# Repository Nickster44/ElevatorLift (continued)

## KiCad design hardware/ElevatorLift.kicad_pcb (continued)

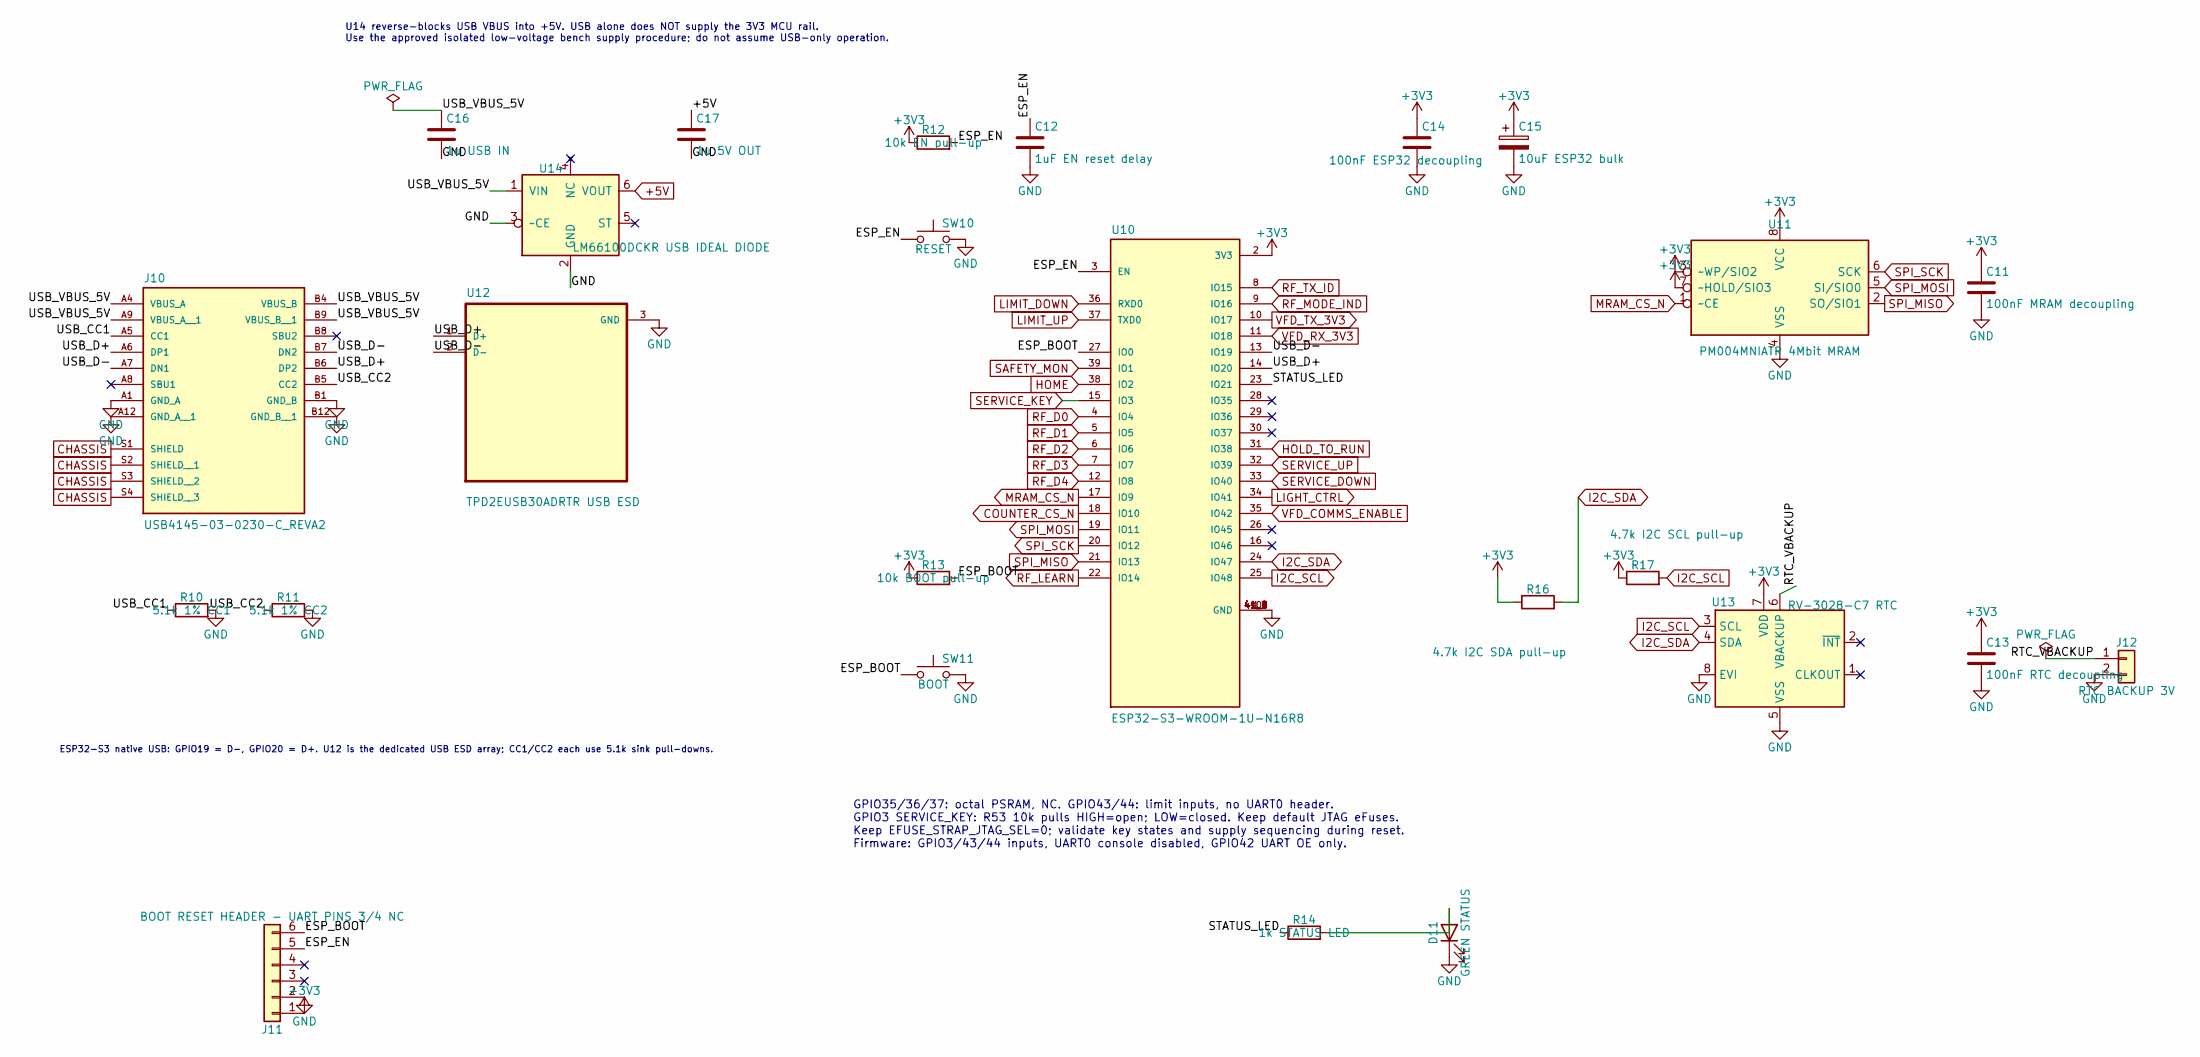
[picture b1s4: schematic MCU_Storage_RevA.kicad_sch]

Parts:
C11: 100nF MRAM decoupling; C_0603_1608Metric
C12: 1uF EN reset delay; C_0603_1608Metric
C13: 100nF RTC decoupling; C_0603_1608Metric
C14: 100nF ESP32 decoupling; C_0603_1608Metric
C15: 10uF ESP32 bulk; C_0805_2012Metric
C16: 1u USB IN; C_0603_1608Metric
C17: 1u 5V OUT; C_0603_1608Metric
D11: GREEN STATUS; LED_0603_1608Metric
J10: USB4145-03-0230-C_REVA2; GCT_USB4145-03-0230-C_REVA2
J11: BOOT RESET HEADER - UART PINS 3/4 NC; PinHeader_1x06_P2.54mm_Vertical
J12: RTC BACKUP 3V; PinHeader_1x02_P2.54mm_Vertical
R10: 5.1k 1% CC1; R_0603_1608Metric
R11: 5.1k 1% CC2; R_0603_1608Metric
R12: 10k EN pull-up; R_0603_1608Metric
R13: 10k BOOT pull-up; R_0603_1608Metric
R14: 1k STATUS LED; R_0603_1608Metric
R16: 4.7k I2C SDA pull-up; R_0603_1608Metric
R17: 4.7k I2C SCL pull-up; R_0603_1608Metric
SW10: RESET; SW_SPST_PTS810
SW11: BOOT; SW_SPST_PTS810
U10: ESP32-S3-WROOM-1U-N16R8; ESP32-S3-WROOM-1U-N16R8_CorrectedV2; MPN ESP32-S3-WROOM-1U-N16R8
U11: PM004MNIATR 4Mbit MRAM; SOIC-8_3.9x4.9mm_P1.27mm; MPN PM004MNIATR
U12: TPD2EUSB30ADRTR USB ESD; SOTFL35P100X50-3N; MPN TPD2EUSB30ADRTR
U13: RV-3028-C7 RTC; MicroCrystal_C7_SON-8_1.5x3.2mm_P0.9mm; MPN RV-3028-C7
U14: LM66100DCKR USB IDEAL DIODE; SOT-363_SC-70-6; MPN LM66100DCKR

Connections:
+3V3: C11.1, C13.1, C14.1, C15.1, J11.1, R12.1, R13.1, R16.1, R17.1, U10.2 (3V3), U11.3 (~WP/SIO2), U11.7 (~HOLD/SIO3), U11.8 (VCC), U13.7 (VDD); also elsewhere on the board
+5V: C17.1, U14.6 (VOUT); also elsewhere on the board
/MCU_Storage/ESP_BOOT: J11.6, R13.2, SW11.1, U10.27 (IO0)
/MCU_Storage/ESP_EN: C12.1, J11.5, R12.2, SW10.1, U10.3 (EN)
/MCU_Storage/RTC_VBACKUP: J12.1, U13.6 (VBACKUP)
/MCU_Storage/STATUS_LED: R14.1, U10.23 (IO21)
/MCU_Storage/USB_CC1: J10.A5 (CC1), R10.1
/MCU_Storage/USB_CC2: J10.B5 (CC2), R11.1
/MCU_Storage/USB_D+: J10.A6 (DP1), J10.B6 (DP2), U10.14 (IO20), U12.1 (D+)
/MCU_Storage/USB_D-: J10.A7 (DN1), J10.B7 (DN2), U10.13 (IO19), U12.2 (D-)
/MCU_Storage/USB_VBUS_5V: C16.1, J10.A4 (VBUS_A), J10.A9 (VBUS_A__1), J10.B4 (VBUS_B), J10.B9 (VBUS_B__1), U14.1 (VIN)
CHASSIS: J10.S1 (SHIELD), J10.S2 (SHIELD__1), J10.S3 (SHIELD__2), J10.S4 (SHIELD__3); also elsewhere on the board
COUNTER_CS_N: U10.18 (IO10); also elsewhere on the board
GND: C11.2, C12.2, C13.2, C14.2, C15.2, C16.2, C17.2, D11.1 (K), J10.A1 (GND_A), J10.A12 (GND_A__1), J10.B1 (GND_B), J10.B12 (GND_B__1), J11.2, J12.2, R10.2, R11.2, SW10.2, SW11.2, U10.1 (GND), U10.40 (GND), U10.41_1 (GND), U10.41_2 (GND), U10.41_3 (GND), U10.41_4 (GND), U10.41_5 (GND), U10.41_6 (GND), U10.41_7 (GND), U10.41_8 (GND), U10.41_9 (GND), U11.4 (VSS), U12.3 (GND), U13.5 (VSS), U13.8 (EVI), U14.2 (GND), U14.3 (~CE); also elsewhere on the board
HOLD_TO_RUN: U10.31 (IO38); also elsewhere on the board
HOME: U10.38 (IO2); also elsewhere on the board
I2C_SCL: R17.2, U10.25 (IO48), U13.3 (SCL)
I2C_SDA: R16.2, U10.24 (IO47), U13.4 (SDA)
LIGHT_CTRL: U10.34 (IO41); also elsewhere on the board
LIMIT_DOWN: U10.36 (RXD0); also elsewhere on the board
LIMIT_UP: U10.37 (TXD0); also elsewhere on the board
MRAM_CS_N: U10.17 (IO9), U11.1 (~CE)
unnamed: D11.2 (A), R14.2
RF_D0: U10.4 (IO4); also elsewhere on the board
RF_D1: U10.5 (IO5); also elsewhere on the board
RF_D2: U10.6 (IO6); also elsewhere on the board
RF_D3: U10.7 (IO7); also elsewhere on the board
RF_D4: U10.12 (IO8); also elsewhere on the board
RF_LEARN: U10.22 (IO14); also elsewhere on the board
RF_MODE_IND: U10.9 (IO16); also elsewhere on the board
RF_TX_ID: U10.8 (IO15); also elsewhere on the board
SAFETY_MON: U10.39 (IO1); also elsewhere on the board
SERVICE_DOWN: U10.33 (IO40); also elsewhere on the board
SERVICE_KEY: U10.15 (IO3); also elsewhere on the board
SERVICE_UP: U10.32 (IO39); also elsewhere on the board
SPI_MISO: U10.21 (IO13), U11.2 (SO/SIO1); also elsewhere on the board
SPI_MOSI: U10.19 (IO11), U11.5 (SI/SIO0); also elsewhere on the board
SPI_SCK: U10.20 (IO12), U11.6 (SCK); also elsewhere on the board
VFD_COMMS_ENABLE: U10.35 (IO42); also elsewhere on the board
VFD_RX_3V3: U10.11 (IO18); also elsewhere on the board
VFD_TX_3V3: U10.10 (IO17); also elsewhere on the board

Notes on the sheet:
GPIO35/36/37: octal PSRAM, NC. GPIO43/44: limit inputs, no UART0 header. GPIO3 SERVICE_KEY: R53 10k pulls HIGH=open; LOW=closed. Keep default JTAG eFuses. Keep EFUSE_STRAP_JTAG_SEL=0; validate key states and supply sequencing during reset. Firmware: GPIO3/43/44 inputs, UART0 console disabled, GPIO4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
U14 reverse-blocks USB VBUS into +5V. USB alone does NOT supply the 3V3 MCU rail. Use the approved isolated low-voltage bench supply procedure; do not assume USB-only operation.
ESP32-S3 native USB: GPIO19 = D-, GPIO20 = D+. U12 is the dedicated USB ESD array; CC1/CC2 each use 5.1k sink pull-downs.

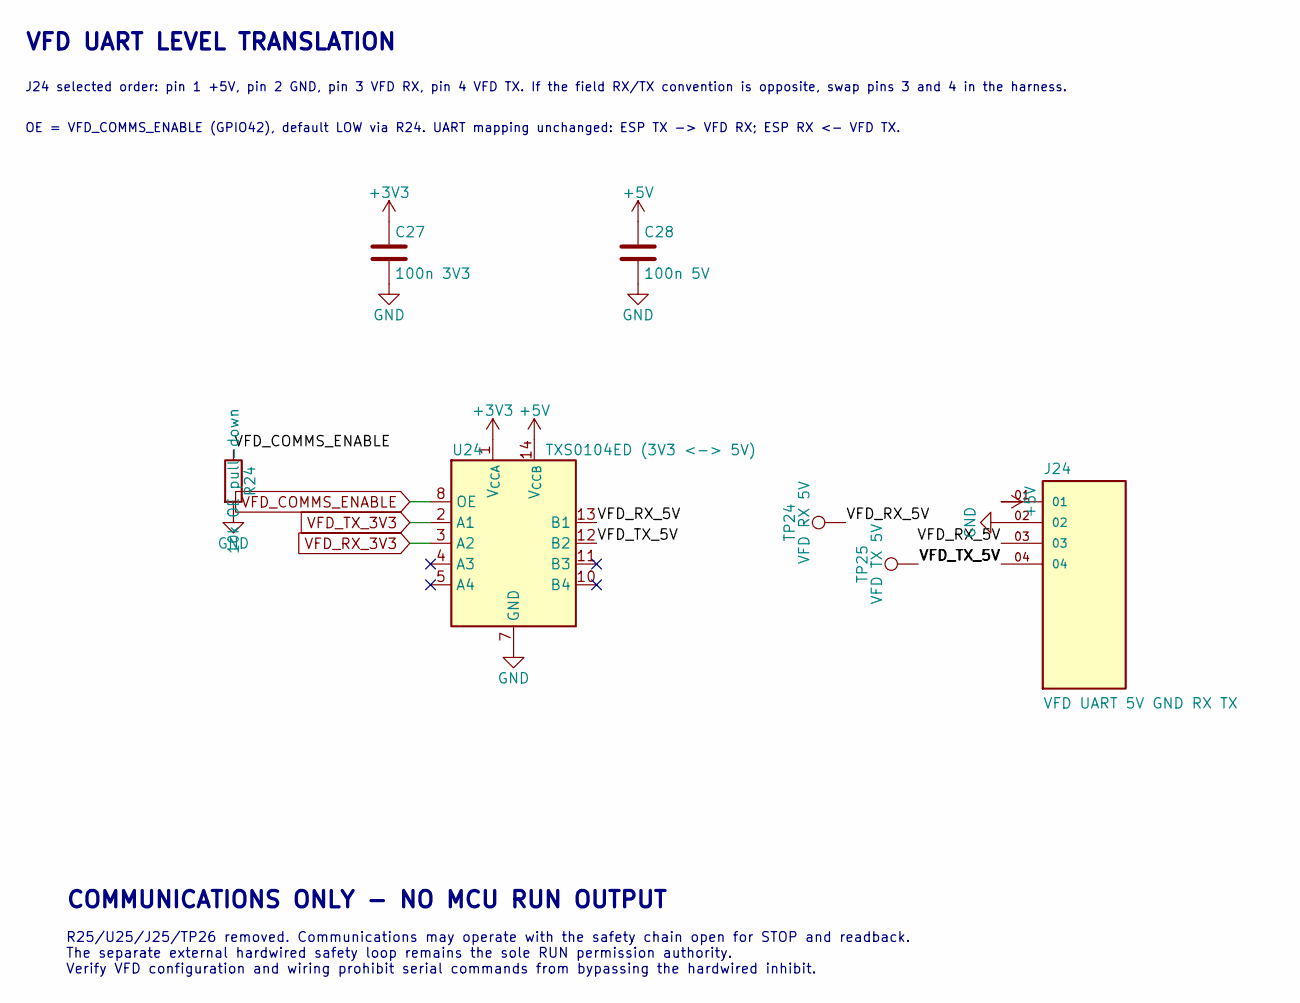
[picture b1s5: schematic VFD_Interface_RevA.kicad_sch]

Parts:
C27: 100n 3V3; C_0603_1608Metric
C28: 100n 5V; C_0603_1608Metric
J24: VFD UART 5V GND RX TX; SAMTEC_TSW-104-07-G-S_ZeroPadded
R24: 10k OE pull-down; R_0603_1608Metric
TP24: VFD RX 5V; TestPoint_Pad_D1.0mm
TP25: VFD TX 5V; TestPoint_Pad_D1.0mm
U24: TXS0104ED (3V3 <-> 5V); SOIC-14_3.9x8.7mm_P1.27mm; MPN TXS0104EDR

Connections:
+3V3: C27.1, U24.1 (V_{CCA}); also elsewhere on the board
+5V: C28.1, J24.01, U24.14 (V_{CCB}); also elsewhere on the board
/VFD_Interface/VFD_RX_5V: J24.03, TP24.1 (1_1), U24.13 (B1)
/VFD_Interface/VFD_TX_5V: J24.04, TP25.1 (1_1), U24.12 (B2)
GND: C27.2, C28.2, J24.02, R24.2, U24.7 (GND); also elsewhere on the board
VFD_COMMS_ENABLE: R24.1, U24.8 (OE); also elsewhere on the board
VFD_RX_3V3: U24.3 (A2); also elsewhere on the board
VFD_TX_3V3: U24.2 (A1); also elsewhere on the board

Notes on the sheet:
J24 selected order: pin 1 +5V, pin 2 GND, pin 3 VFD RX, pin 4 VFD TX. If the field RX/TX convention is opposite, swap pins 3 and 4 in the harness.
COMMUNICATIONS ONLY - NO MCU RUN OUTPUT
OE = VFD_COMMS_ENABLE (GPIO42), default LOW via R24. UART mapping unchanged: ESP TX -> VFD RX; ESP RX <- VFD TX.
VFD UART LEVEL TRANSLATION
R25/U25/J25/TP26 removed. Communications may operate with the safety chain open for STOP and readback. The separate external hardwired safety loop remains the sole RUN permission authority. Verify VFD configuration and wiring prohibit serial commands from bypassing the hardwired inhibit.

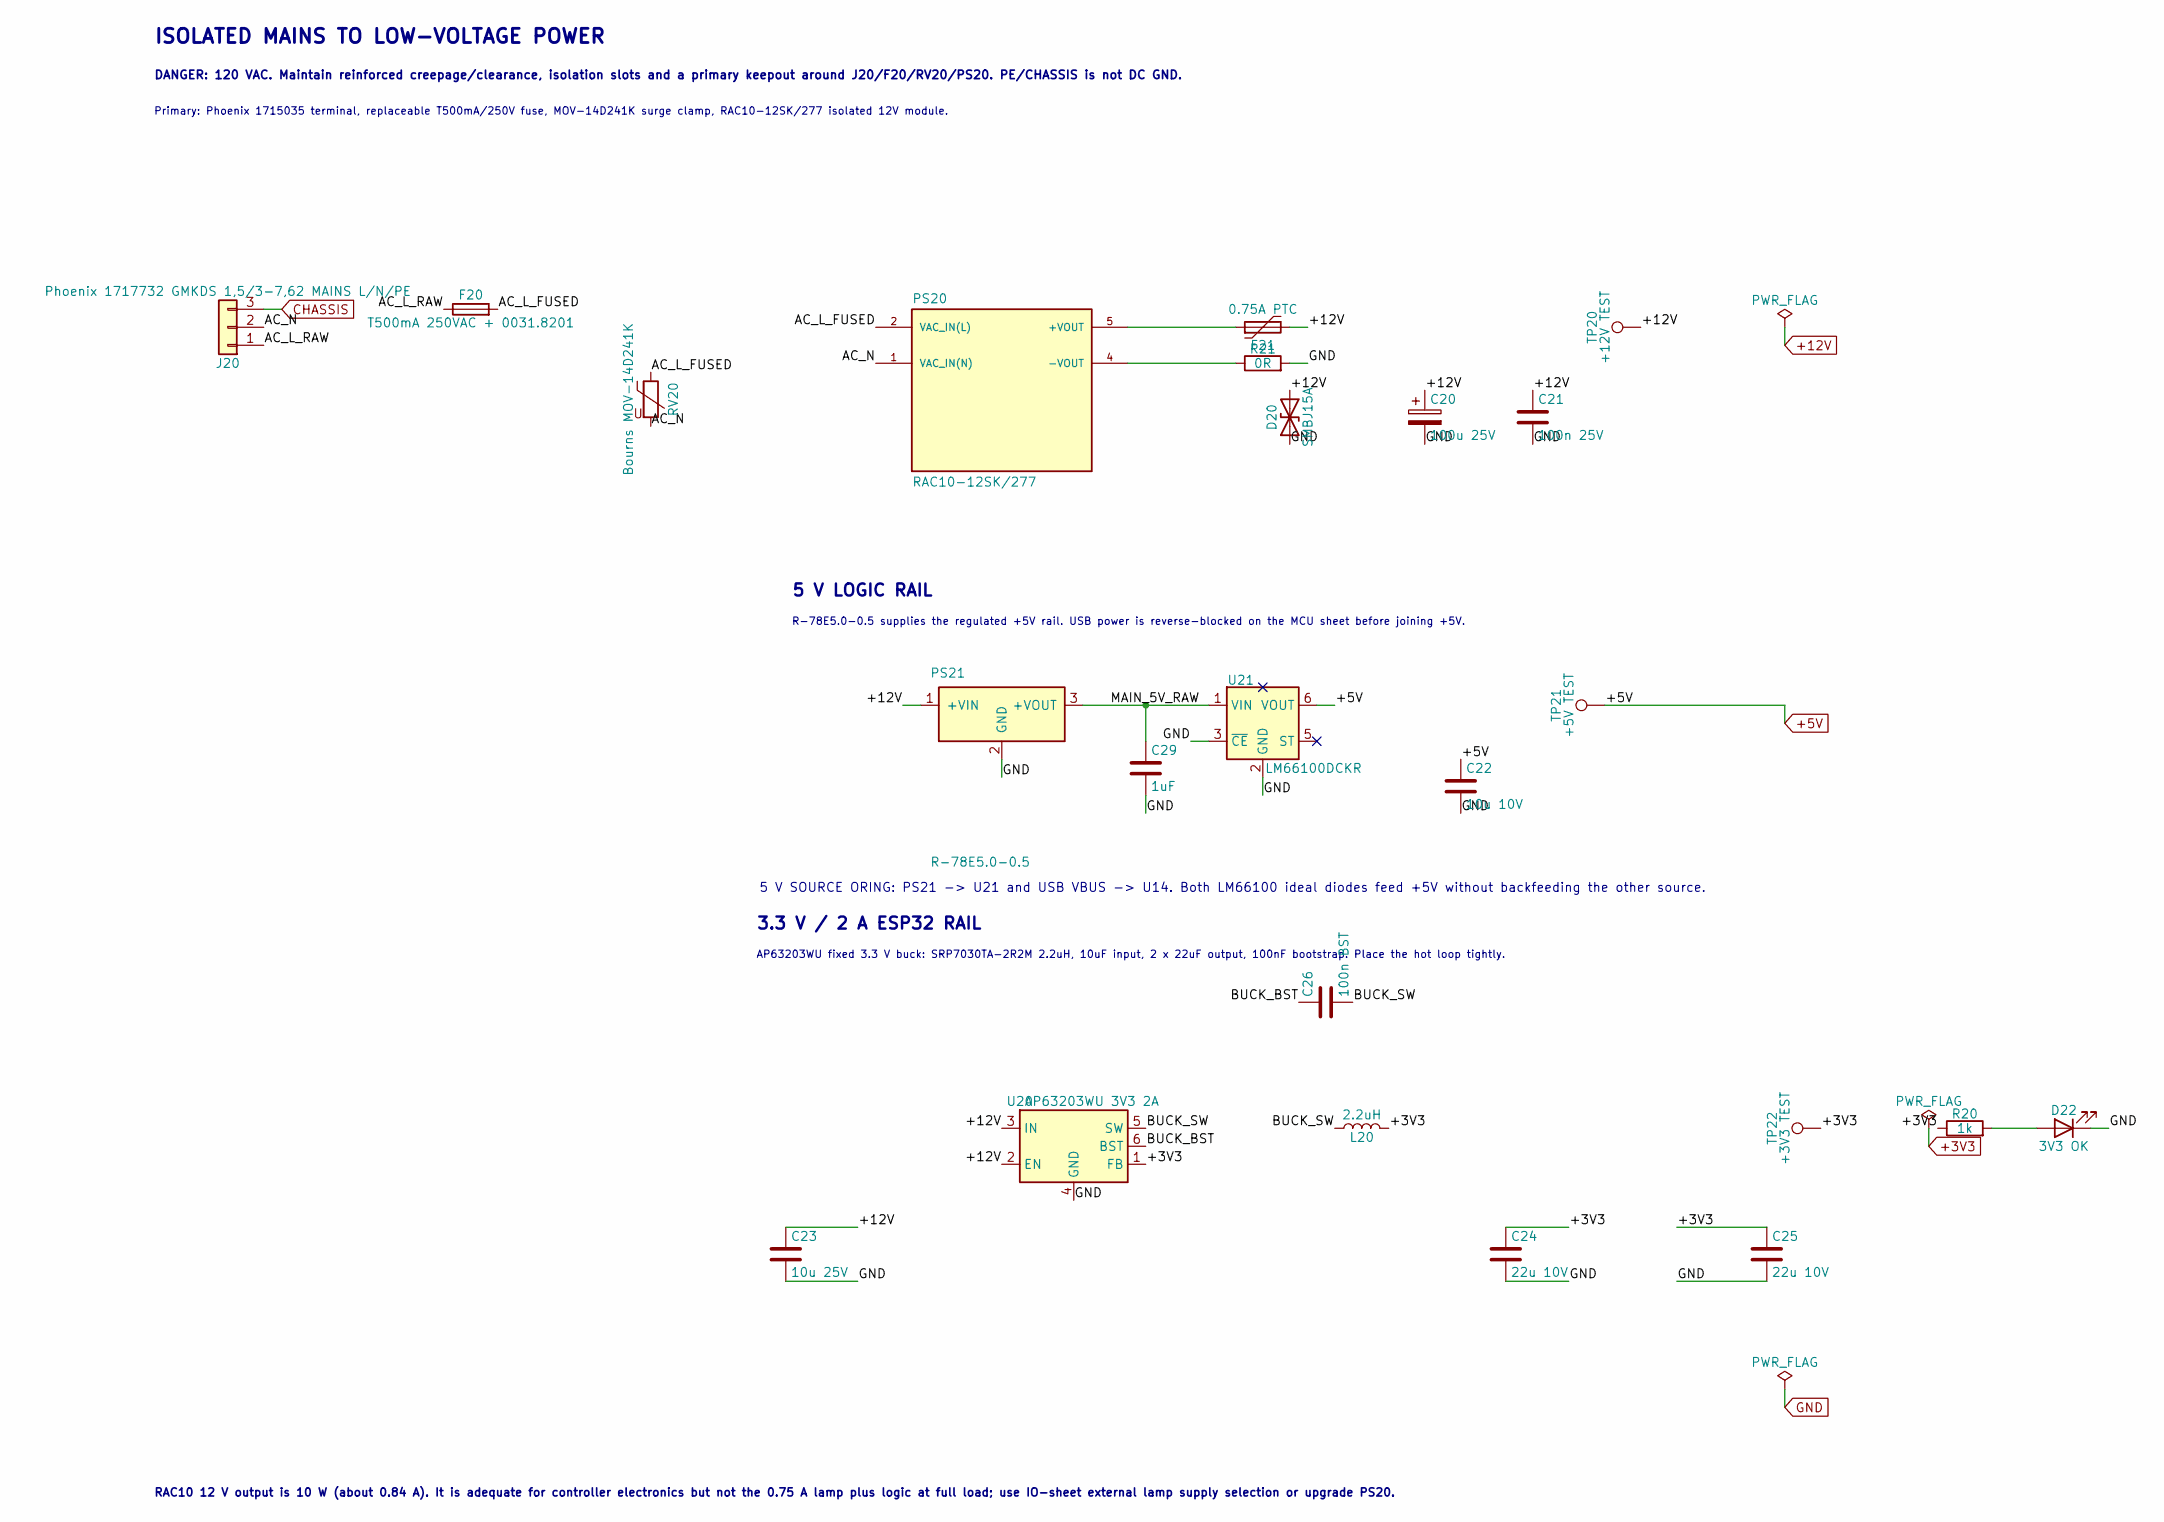
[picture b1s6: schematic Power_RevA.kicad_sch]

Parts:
C20: 100u 25V; CP_Radial_D8.0mm_P3.50mm
C21: 100n 25V; C_0603_1608Metric
C22: 10u 10V; C_0805_2012Metric
C23: 10u 25V; C_1206_3216Metric
C24, C25: 22u 10V; C_1206_3216Metric
C26: 100n BST; C_0603_1608Metric
C29: 1uF; C_0603_1608Metric
D20: SMBJ15A; D_SMB
D22: 3V3 OK; LED_0603_1608Metric
F20: T500mA 250VAC + 0031.8201; Fuseholder_Cylinder-5x20mm_Schurter_0031_8201_Horizontal_Op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
F21: 0.75A PTC; Fuse_1812_4532Metric; MPN MF-MSMF075/24X
J20: Phoenix 1717732 GMKDS 1,5/3-7,62 MAINS L/N/PE; Phoenix_GMKDS-1.5-3-7.62_1717732_Provisional
L20: 2.2uH; L_Bourns_SRP7028A_7.3x6.6mm; MPN SRP7028A-2R2M
PS20: RAC10-12SK/277; CONV_RAC10-12SK_277
PS21: R-78E5.0-0.5; CONV_R-78E5.0-0.5
R20: 1k; R_0603_1608Metric
R21: 0R; R_0603_1608Metric
RV20: Bourns MOV-14D241K; RV_Disc_D15.5mm_W5.2mm_P7.5mm
TP20: +12V TEST; TestPoint_Pad_D1.0mm
TP21: +5V TEST; TestPoint_Pad_D1.0mm
TP22: +3V3 TEST; TestPoint_Pad_D1.0mm
U20: AP63203WU 3V3 2A; TSOT-23-6; MPN AP63203WU-7
U21: LM66100DCKR; SOT-363_SC-70-6; MPN LM66100DCKR

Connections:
+3V3: C24.1, C25.1, L20.2, R20.1, TP22.1 (1_1), U20.1 (FB); also elsewhere on the board
+5V: C22.1, TP21.1 (1_1), U21.6 (VOUT); also elsewhere on the board
+12V: C20.1, C21.1, C23.1, D20.2 (A2), F21.2, PS21.1 (+VIN), TP20.1 (1_1), U20.2 (EN), U20.3 (IN); also elsewhere on the board
/Power/AC_L_FUSED: F20.2, PS20.2 (VAC_IN(L)), RV20.1
/Power/AC_L_RAW: F20.1, J20.1
/Power/AC_N: J20.2, PS20.1 (VAC_IN(N)), RV20.2
/Power/BUCK_BST: C26.1, U20.6 (BST)
/Power/BUCK_SW: C26.2, L20.1, U20.5 (SW)
/Power/MAIN_5V_RAW: C29.1, PS21.3 (+VOUT), U21.1 (VIN)
CHASSIS: J20.3; also elsewhere on the board
GND: C20.2, C21.2, C22.2, C23.2, C24.2, C25.2, C29.2, D20.1 (A1), D22.1 (K), PS21.2 (GND), R21.2, U20.4 (GND), U21.2 (GND), U21.3 (~CE); also elsewhere on the board
unnamed: D22.2 (A), R20.2
unnamed: F21.1, PS20.5 (+VOUT)
unnamed: PS20.4 (-VOUT), R21.1

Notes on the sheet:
ISOLATED MAINS TO LOW-VOLTAGE POWER
5 V LOGIC RAIL
3.3 V / 2 A ESP32 RAIL
Primary: Phoenix 1715035 terminal, replaceable T500mA/250V fuse, MOV-14D241K surge clamp, RAC10-12SK/277 isolated 12V module.
AP63203WU fixed 3.3 V buck: SRP7030TA-2R2M 2.2uH, 10uF input, 2 x 22uF output, 100nF bootstrap. Place the hot loop tightly.
DANGER: 120 VAC. Maintain reinforced creepage/clearance, isolation slots and a primary keepout around J20/F20/RV20/PS20. PE/CHASSIS is not DC GND.
5 V SOURCE ORING: PS21 -> U21 and USB VBUS -> U14. Both LM66100 ideal diodes feed +5V without backfeeding the other source.
R-78E5.0-0.5 supplies the regulated +5V rail. USB power is reverse-blocked on the MCU sheet before joining +5V.
RAC10 12 V output is 10 W (about 0.84 A). It is adequate for controller electronics but not the 0.75 A lamp plus logic at full load; use IO-sheet external lamp supply selection or upgrade PS20.

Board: 4 copper layers, 126 parts (51 on the bottom side), 92 nets, no tracks yet.
